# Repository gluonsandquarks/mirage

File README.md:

# Mirage

Custom PCB board inspired by the [#badgelife](https://www.youtube.com/watch?v=G2fHKRONc6U) and PCB Art movement. The "Mirage" badge represents to me a kind of miracle because it demonstrates that without prior knowledge, thanks to all the available free information out there, it is possible to build systems from scratch and, on top of that, style them and express ourselves.

The art of the board itself is NOT done by me, it's all done by the wonderful [@OseanWorld](https://twitter.com/oseanworld). Huge props to Osean for keeping me and everyone in the community dreaming and doing art, and thanks for creating such a beautiful cyberspace.

## Hardware

The modules and components used in this board are the following:
- ESP32-PICO-D4: MCU + BLE transciever.
- CP2102-GMR: USB-to-UART converter. Needed to upload code and debug via UART.
- S8050 NPN transistors: needed to detect automatically when code is being uploaded to the MCU. 
- AMS1117-3.3: 5V to 3.3V regulator.
- AO3401A P channel MOSFET: works as reverse polarity protection.
- USBLC6-2SC6: diode array for ESD protection.
- M7 Diode.
- USB Mini B connector.
- 1 push buttons.
- Shitload of capacitors, resistors, LEDs.

All the references and datasheets of the components used in the schematic can be found in the `/datasheets` directory.

If you want to learn the technicalities of designing a PCB yourself you can checkout [Phil's Lab youtube channel](https://www.youtube.com/c/PhilS94) for an intro to PCB design.

### RF Section
The design includes an RF portion which is *"designed"* for BLE communications. With "designed" being in quotes because this is my first RF design and my first time making a PCB trace antenna. The hard truth about RF is that there's no real way of tuning the antenna or making a matching Pi Network without some sort of expensive equipment (although the NanoVNAs are pretty cheap nowadays). I don't have access to these tools so I just winged it by calculating a 50 Ohm impedance microstrip line and using a 0 Ohm resistor as a jumper wire. The antenna trace is between 20 mm - 25 mm in length (given the 2.45 GHz frequency of BLE) but it's a mess right now and I don't know if it will work at all. I'll update this section once the PCBs arrive and I've written some firmware to make two boards talk to each other. 

## Firmware

## Art
The art of this board was made entirely inside Inkscape and ported to KiCad thanks to the [svg2shenzhen](https://github.com/badgeek/svg2shenzhen) extension made by [@badgeek](https://github.com/badgeek). Also the great [video tutorial](https://www.youtube.com/watch?v=Sbkvza8cKQE) done by [@mrtwinkletwink](https://twitter.com/mrtwinkletwink) helped me a lot when it came to understand the different layers of the board and how to use svg2shenzhen in general.

## Directory Structure
As you can see, right now the repo is pretty unorganized. Maybe I'll restructure it in the future, but as of now here are the main files:

- **\*.kicad**: This files contain all the relevant design for the electrical part of the board. The *.kicad_pro* file is the main file you'll want to open (by double clicking on it). The *.kicad_sch* contains the schematic for the board. The *kicad_pcb* contains the layout for the components and the overall PCB design.
- **nudeko.pretty**: contains the custom PCB outline, silkscreen and copper layers which done in Inkscape. *You'll have to load this module into your footprint library if KiCad doesn't do that automatically.*
- **nudeko.svg**: This file contains the vector art. It was done in Inkscape and the document was prepared and imported to KiCad with the [svg2shenzhen](https://github.com/badgeek/svg2shenzhen) extension made by [@badgeek](https://github.com/badgeek).
- **symbols**: This directory contains a custom library I made for KiCad. It only contains the M7 diode footprint. If KiCad doesn't recognize this automatically you'll have to tell it where it's located.
- **nudekoINK2KICAD**: Contains the files generated by the svg2shenzhen extension. Might delete this in the future cause it only adds junk to the repo.
- **datasheets**: As its name implies, here are the datasheets of each component I used for the electronics (aside from passive components). You could use other components if you know what you're doing but this is what was in stock (or was a basic part for the most part) at [JLCPCB](https://jlcpcb.com/).
- **MirageR1-backups**: Generated automatically by KiCad. Might delete this guys too.

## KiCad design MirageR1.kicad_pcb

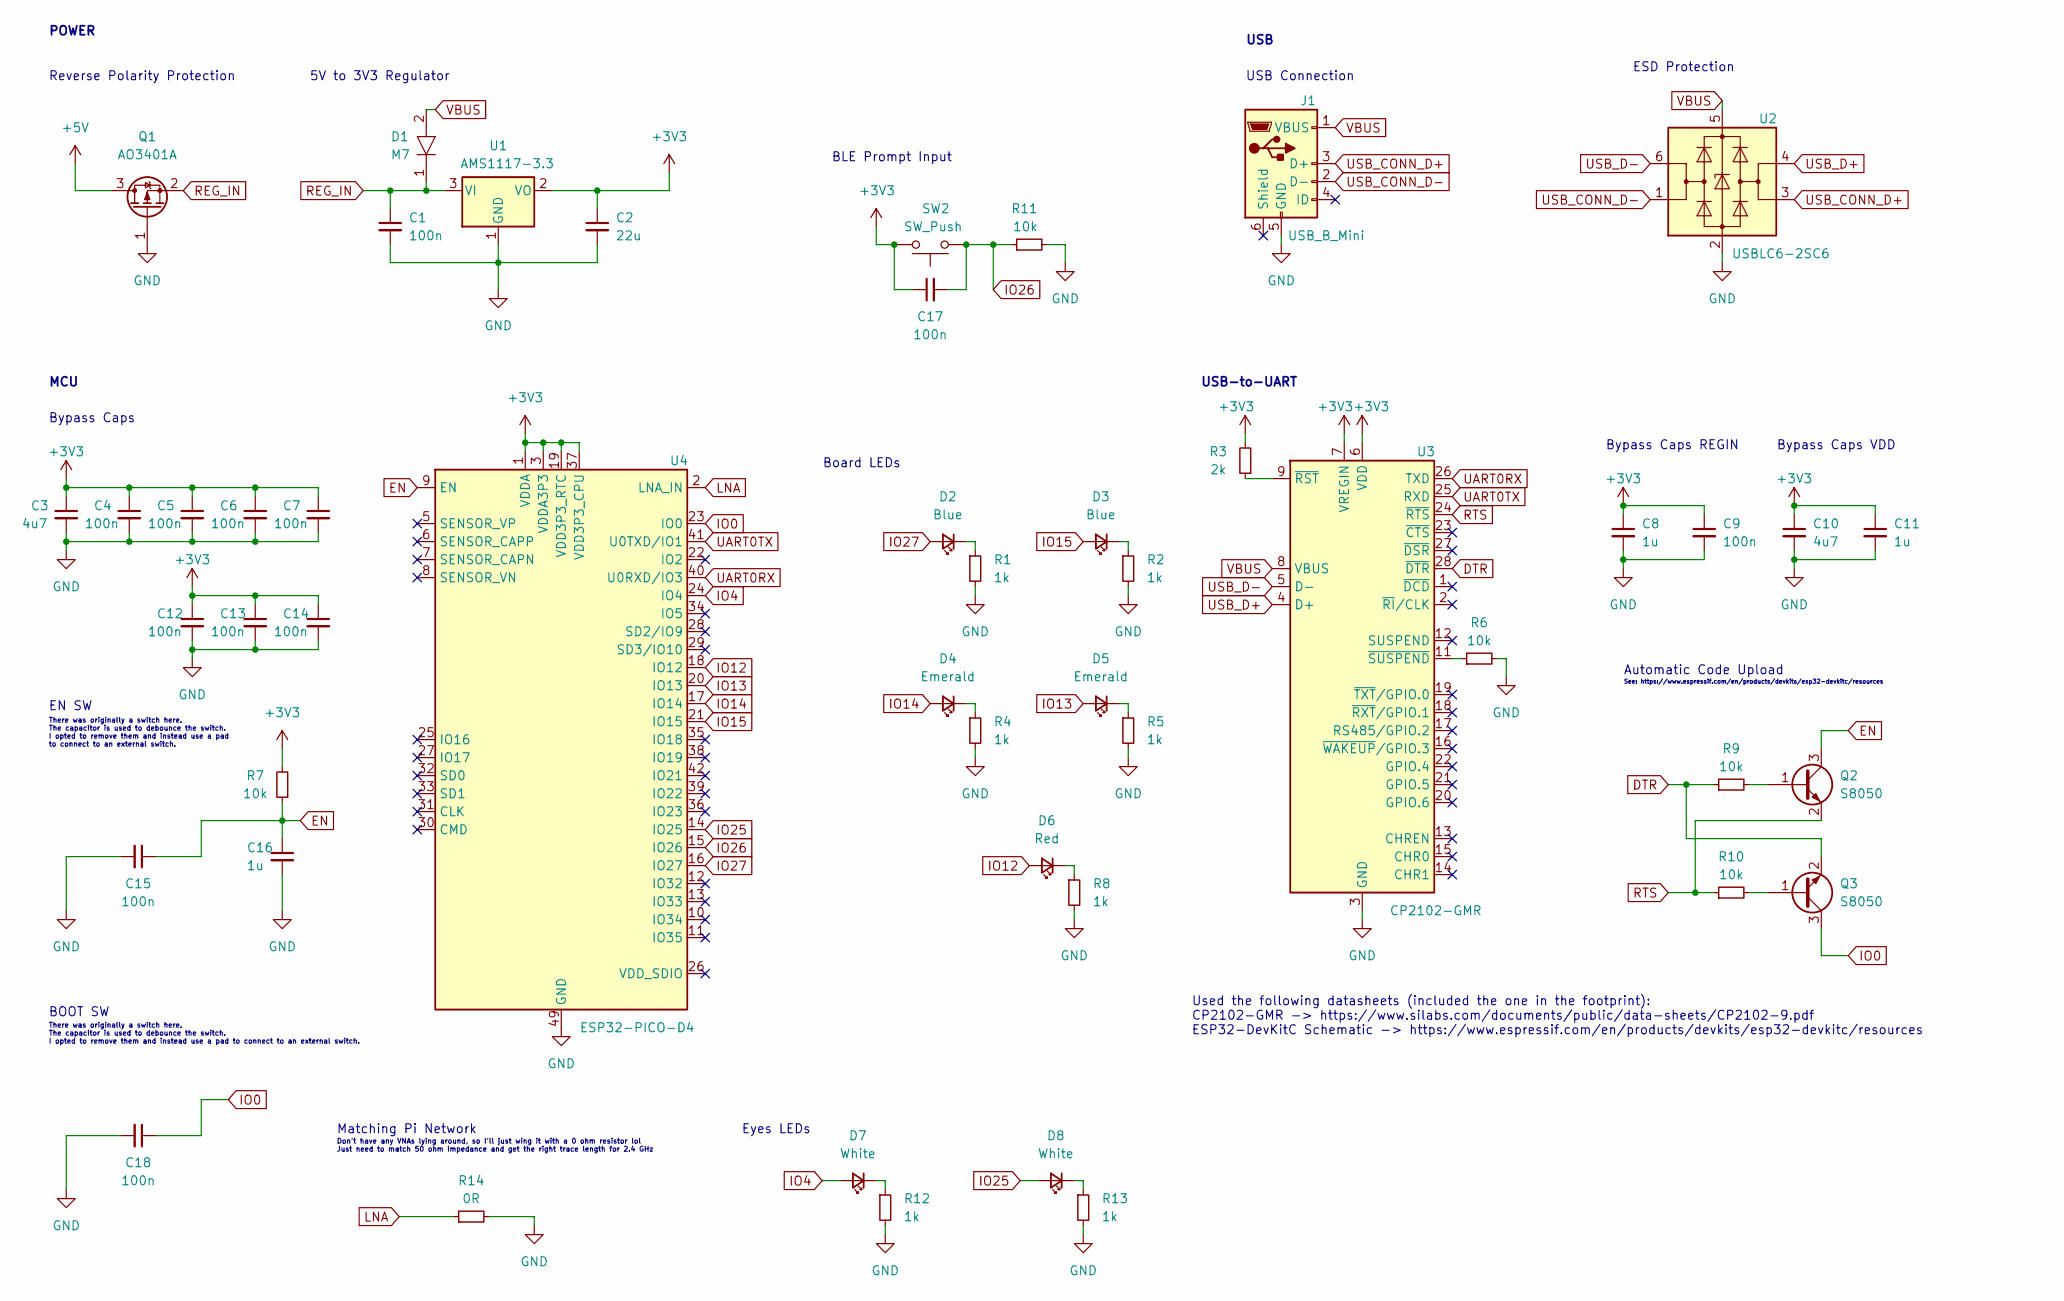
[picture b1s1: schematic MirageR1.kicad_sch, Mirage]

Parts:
C1, C4, C5, C6, C7, C9, C12, C13, C14, C15, C17, C18: 100n; C_0402_1005Metric
C2: 22u; C_0603_1608Metric
C3, C10: 4u7; C_0402_1005Metric
C8, C11, C16: 1u; C_0402_1005Metric
D1: M7; D_MiniMELF
D2, D3: Blue; LED_0805_2012Metric_Pad1.15x1.40mm_HandSolder
D4, D5: Emerald; LED_0805_2012Metric_Pad1.15x1.40mm_HandSolder
D6: Red; LED_0805_2012Metric_Pad1.15x1.40mm_HandSolder
D7, D8: White; LED_0805_2012Metric_Pad1.15x1.40mm_HandSolder
J1: USB_B_Mini; USB_Mini-B_Wuerth_65100516121_Horizontal
Q1: AO3401A; SOT-23
Q2, Q3: S8050; SOT-23
R1, R2, R4, R5, R8, R12, R13: 1k; R_0402_1005Metric
R3: 2k; R_0402_1005Metric
R6, R7, R9, R10, R11: 10k; R_0402_1005Metric
R14: 0R; R_0402_1005Metric
SW2: SW_Push; SW_Push_1P1T_NO_CK_KSC6xxJ
U1: AMS1117-3.3; SOT-223-3_TabPin2
U2: USBLC6-2SC6; SOT-23-6
U3: CP2102-GMR; QFN-28-1EP_5x5mm_P0.5mm_EP3.35x3.35mm
U4: ESP32-PICO-D4; QFN-48-1EP_7x7mm_P0.5mm_EP5.3x5.3mm

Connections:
+3V3: C2.1, C3.1, C4.1, C5.1, C6.1, C7.1, C8.1, C9.1, C10.1, C11.1, C12.1, C13.1, C14.1, C17.1, R3.2, R7.2, SW2.2, U1.2 (VO), U3.6 (VDD), U3.7 (VREGIN), U4.1 (VDDA), U4.3 (VDDA3P3), U4.4 (VDDA3P3), U4.19 (VDD3P3_RTC), U4.37 (VDD3P3_CPU), U4.43 (VDDA), U4.46 (VDDA)
+5V: Q1.3 (D)
DTR: Q3.2 (E), R9.1, U3.28 (~DTR)
EN: C15.1, C16.1, Q2.3 (C), R7.1, U4.9 (EN)
GND: C1.2, C2.2, C3.2, C4.2, C5.2, C6.2, C7.2, C8.2, C9.2, C10.2, C11.2, C12.2, C13.2, C14.2, C15.2, C16.2, C18.2, J1.5 (GND), Q1.1 (G), R1.2, R2.2, R4.2, R5.2, R6.2, R8.2, R11.2, R12.2, R13.2, R14.2, U1.1 (GND), U2.2 (GND), U3.3 (GND), U3.29 (GND), U4.49 (GND)
IO0: C18.1, Q3.3 (C), U4.23 (IO0)
IO4: D7.2 (A), U4.24 (IO4)
IO12: D6.2 (A), U4.18 (IO12)
IO13: D5.2 (A), U4.20 (IO13)
IO14: D4.2 (A), U4.17 (IO14)
IO15: D3.2 (A), U4.21 (IO15)
IO25: D8.2 (A), U4.14 (IO25)
IO26: C17.2, R11.1, SW2.1, U4.15 (IO26)
IO27: D2.2 (A), U4.16 (IO27)
LNA: R14.1, U4.2 (LNA_IN)
unnamed: D2.1 (K), R1.1
unnamed: D3.1 (K), R2.1
unnamed: D4.1 (K), R4.1
unnamed: D5.1 (K), R5.1
unnamed: D6.1 (K), R8.1
unnamed: D7.1 (K), R12.1
unnamed: D8.1 (K), R13.1
unnamed: Q2.1 (B), R9.2
unnamed: Q3.1 (B), R10.2
unnamed: R3.1, U3.9 (~RST)
unnamed: R6.1, U3.11 (~SUSPEND)
REG_IN: C1.1, D1.1, Q1.2 (S), U1.3 (VI)
RTS: Q2.2 (E), R10.1, U3.24 (~RTS)
UART0RX: U3.26 (TXD), U4.40 (U0RXD/IO3)
UART0TX: U3.25 (RXD), U4.41 (U0TXD/IO1)
USB_CONN_D+: J1.3 (D+), U2.3 (I/O2)
USB_CONN_D-: J1.2 (D-), U2.1 (I/O1)
USB_D+: U2.4 (I/O2), U3.4 (D+)
USB_D-: U2.6 (I/O1), U3.5 (D-)
VBUS: D1.2, J1.1 (VBUS), U2.5 (VBUS), U3.8 (VBUS)

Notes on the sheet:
Automatic Code Upload
Bypass Caps
Bypass Caps VDD
EN SW
Used the following datasheets (included the one in the footprint): CP2102-GMR -> https://www.silabs.com/documents/public/data-sheets/CP2102-9.pdf ESP32-DevKitC Schematic -> https://www.espressif.com/en/products/devkits/esp32-devkitc/resources
BLE Prompt Input
Matching Pi Network
There was originally a switch here. The capacitor is used to debounce the switch. I opted to remove them and instead use a pad to connect to an external switch.
5V to 3V3 Regulator
USB-to-UART
There was originally a switch here. The capacitor is used to debounce the switch. I opted to remove them and instead use a pad to connect to an external switch.
BOOT SW
ESD Protection
Bypass Caps REGIN
Eyes LEDs
See: https://www.espressif.com/en/products/devkits/esp32-devkitc/resources
USB Connection
MCU
Don't have any VNAs lying around, so I'll just wing it with a 0 ohm resistor lol Just need to match 50 ohm impedance and get the right trace length for 2.4 GHz
USB
Board LEDs
POWER
Reverse Polarity Protection

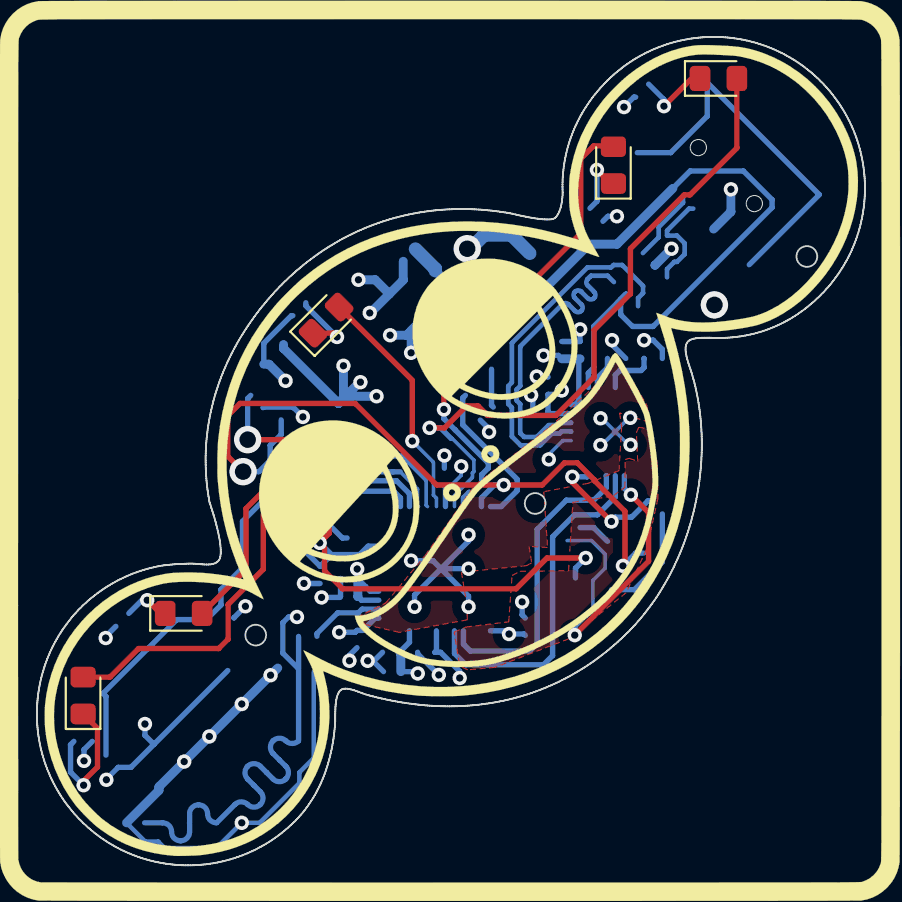
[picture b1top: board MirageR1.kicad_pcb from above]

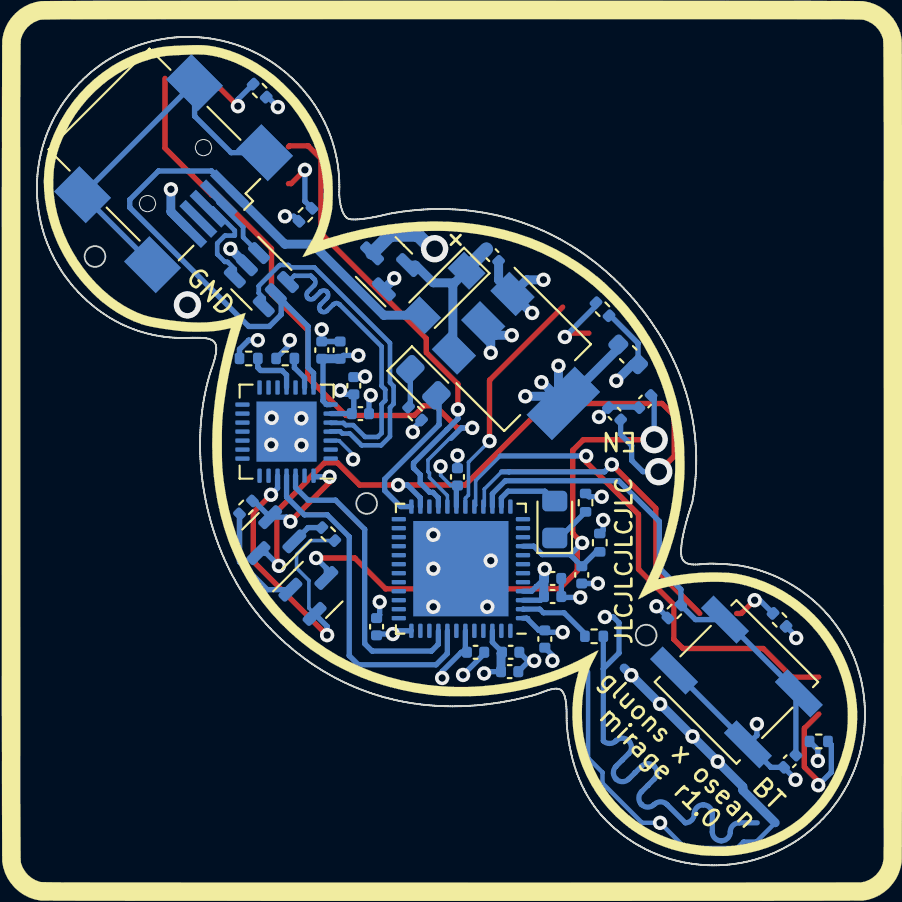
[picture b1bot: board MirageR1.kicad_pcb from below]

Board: 4 copper layers, 46.0 x 46.0 mm, 50 parts (44 on the bottom side), 34 nets.

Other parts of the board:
Ref**: Val**; nudeko

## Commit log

2022-01-23 added license
2022-01-23 added readme
2022-01-23 Update LICENSE
2022-01-26 added mounting pads i guess
2022-02-03 designed the pcb board w/ a 50x50 mm constrain
2022-02-03 modified readme.md
2022-02-03 modified again readme.md
2022-02-04 added different sections to readme.md
2022-02-04 fixed typo
2022-02-08 finished routing, added gerber files, added footprint positioning file, modified the PCB soldermask, did some bad decisions with my life
